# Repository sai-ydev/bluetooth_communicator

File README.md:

# Bluetooth Communicator Badge

This project is my submission for the [Hackaday Sci-Fi Contest](https://hackaday.io/contest/184314-sci-fi-contest). It is a communicator badge from Star Trek. 

It consists of the following components:
1. [BlueNRG-M2SP](https://www.mouser.com/ProductDetail/STMicroelectronics/BLUENRG-M2SP?qs=%252B6g0mu59x7IAMQd6TX9bOA%3D%3D)
2. [BME680](https://www.digikey.com/en/products/detail/bosch-sensortec/BME680/7401317)
3. [LSM6DSO32](https://www.st.com/resource/en/datasheet/lsm6dso32.pdf)

This board can serve two purposes namely: 
1. Pedometer
2. Air Quality Communicator

The first version of the board:

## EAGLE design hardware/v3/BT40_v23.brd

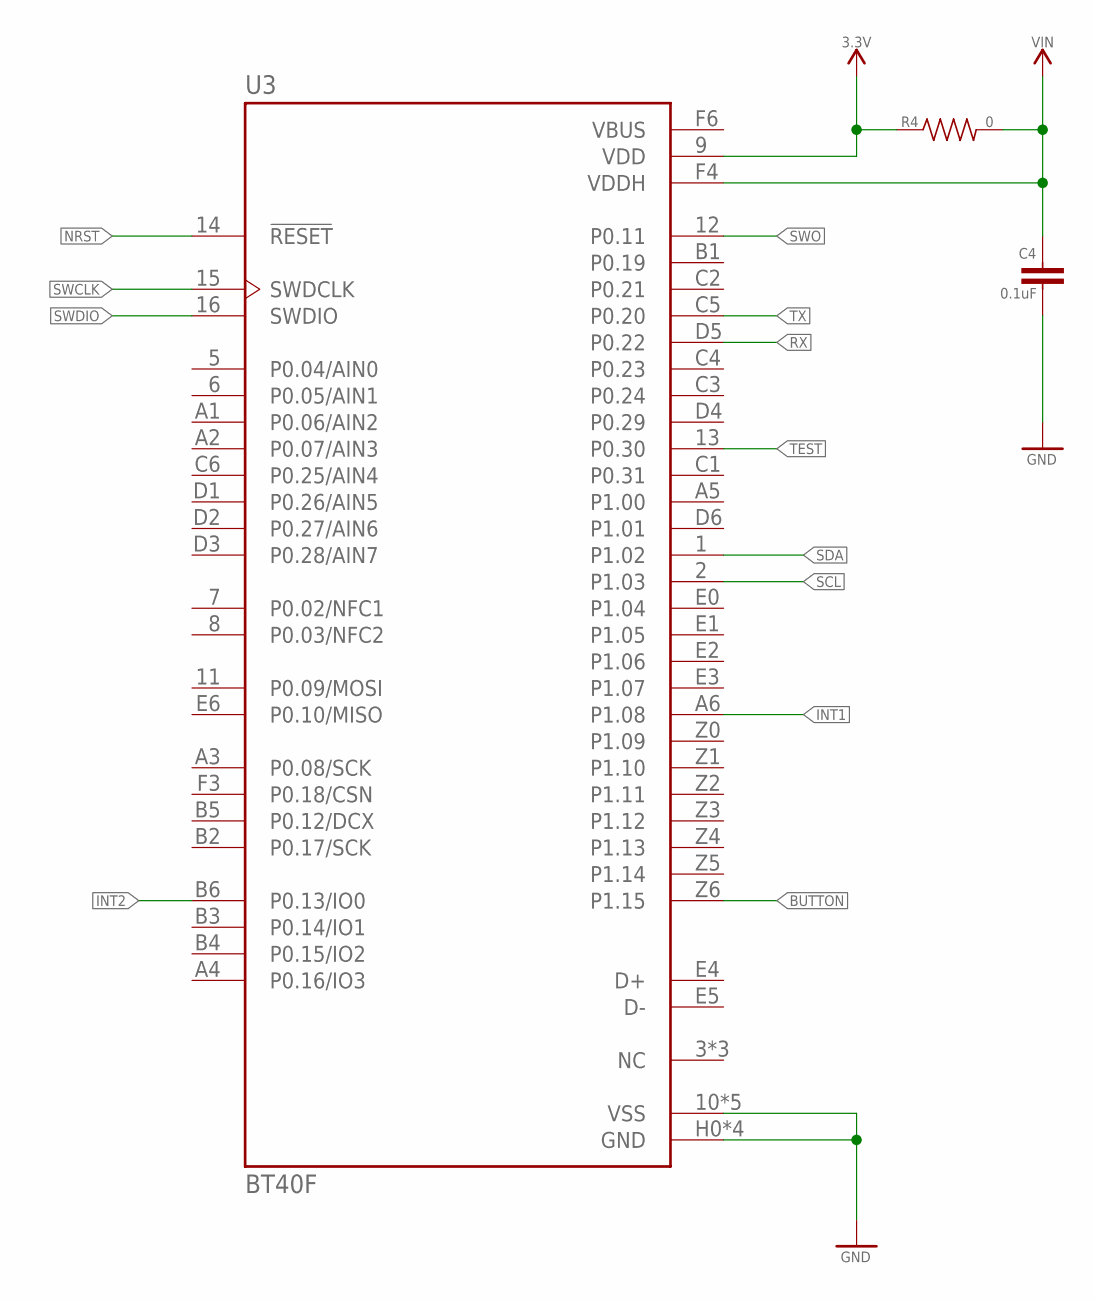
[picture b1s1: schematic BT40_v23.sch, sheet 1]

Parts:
C4: 0.1uF; 0603
R4: 0; 0603
U3: BT40F; XCVR_BT40F

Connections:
3.3V: R4.1, U3.9 (VDD)
BUTTON: U3.Z6 (P1.15); also elsewhere on the board
GND: C4.2, U3.10 (VSS), U3.A0 (VSS), U3.B0 (VSS), U3.C0 (VSS), U3.D0 (VSS), U3.H0 (GND), U3.H1 (GND), U3.H2 (GND), U3.H3 (GND); also elsewhere on the board
INT1: U3.A6 (P1.08); also elsewhere on the board
INT2: U3.B6 (P0.13/IO0); also elsewhere on the board
NRST: U3.14 (!RESET); also elsewhere on the board
RX: U3.D5 (P0.22); also elsewhere on the board
SCL: U3.2 (P1.03); also elsewhere on the board
SDA: U3.1 (P1.02); also elsewhere on the board
SWCLK: U3.15 (SWDCLK); also elsewhere on the board
SWDIO: U3.16 (SWDIO); also elsewhere on the board
SWO: U3.12 (P0.11); also elsewhere on the board
TEST: U3.13 (P0.30); also elsewhere on the board
TX: U3.C5 (P0.20); also elsewhere on the board
VBUS: U3.F6 (VBUS)
VIN: C4.1, R4.2, U3.F4 (VDDH); also elsewhere on the board

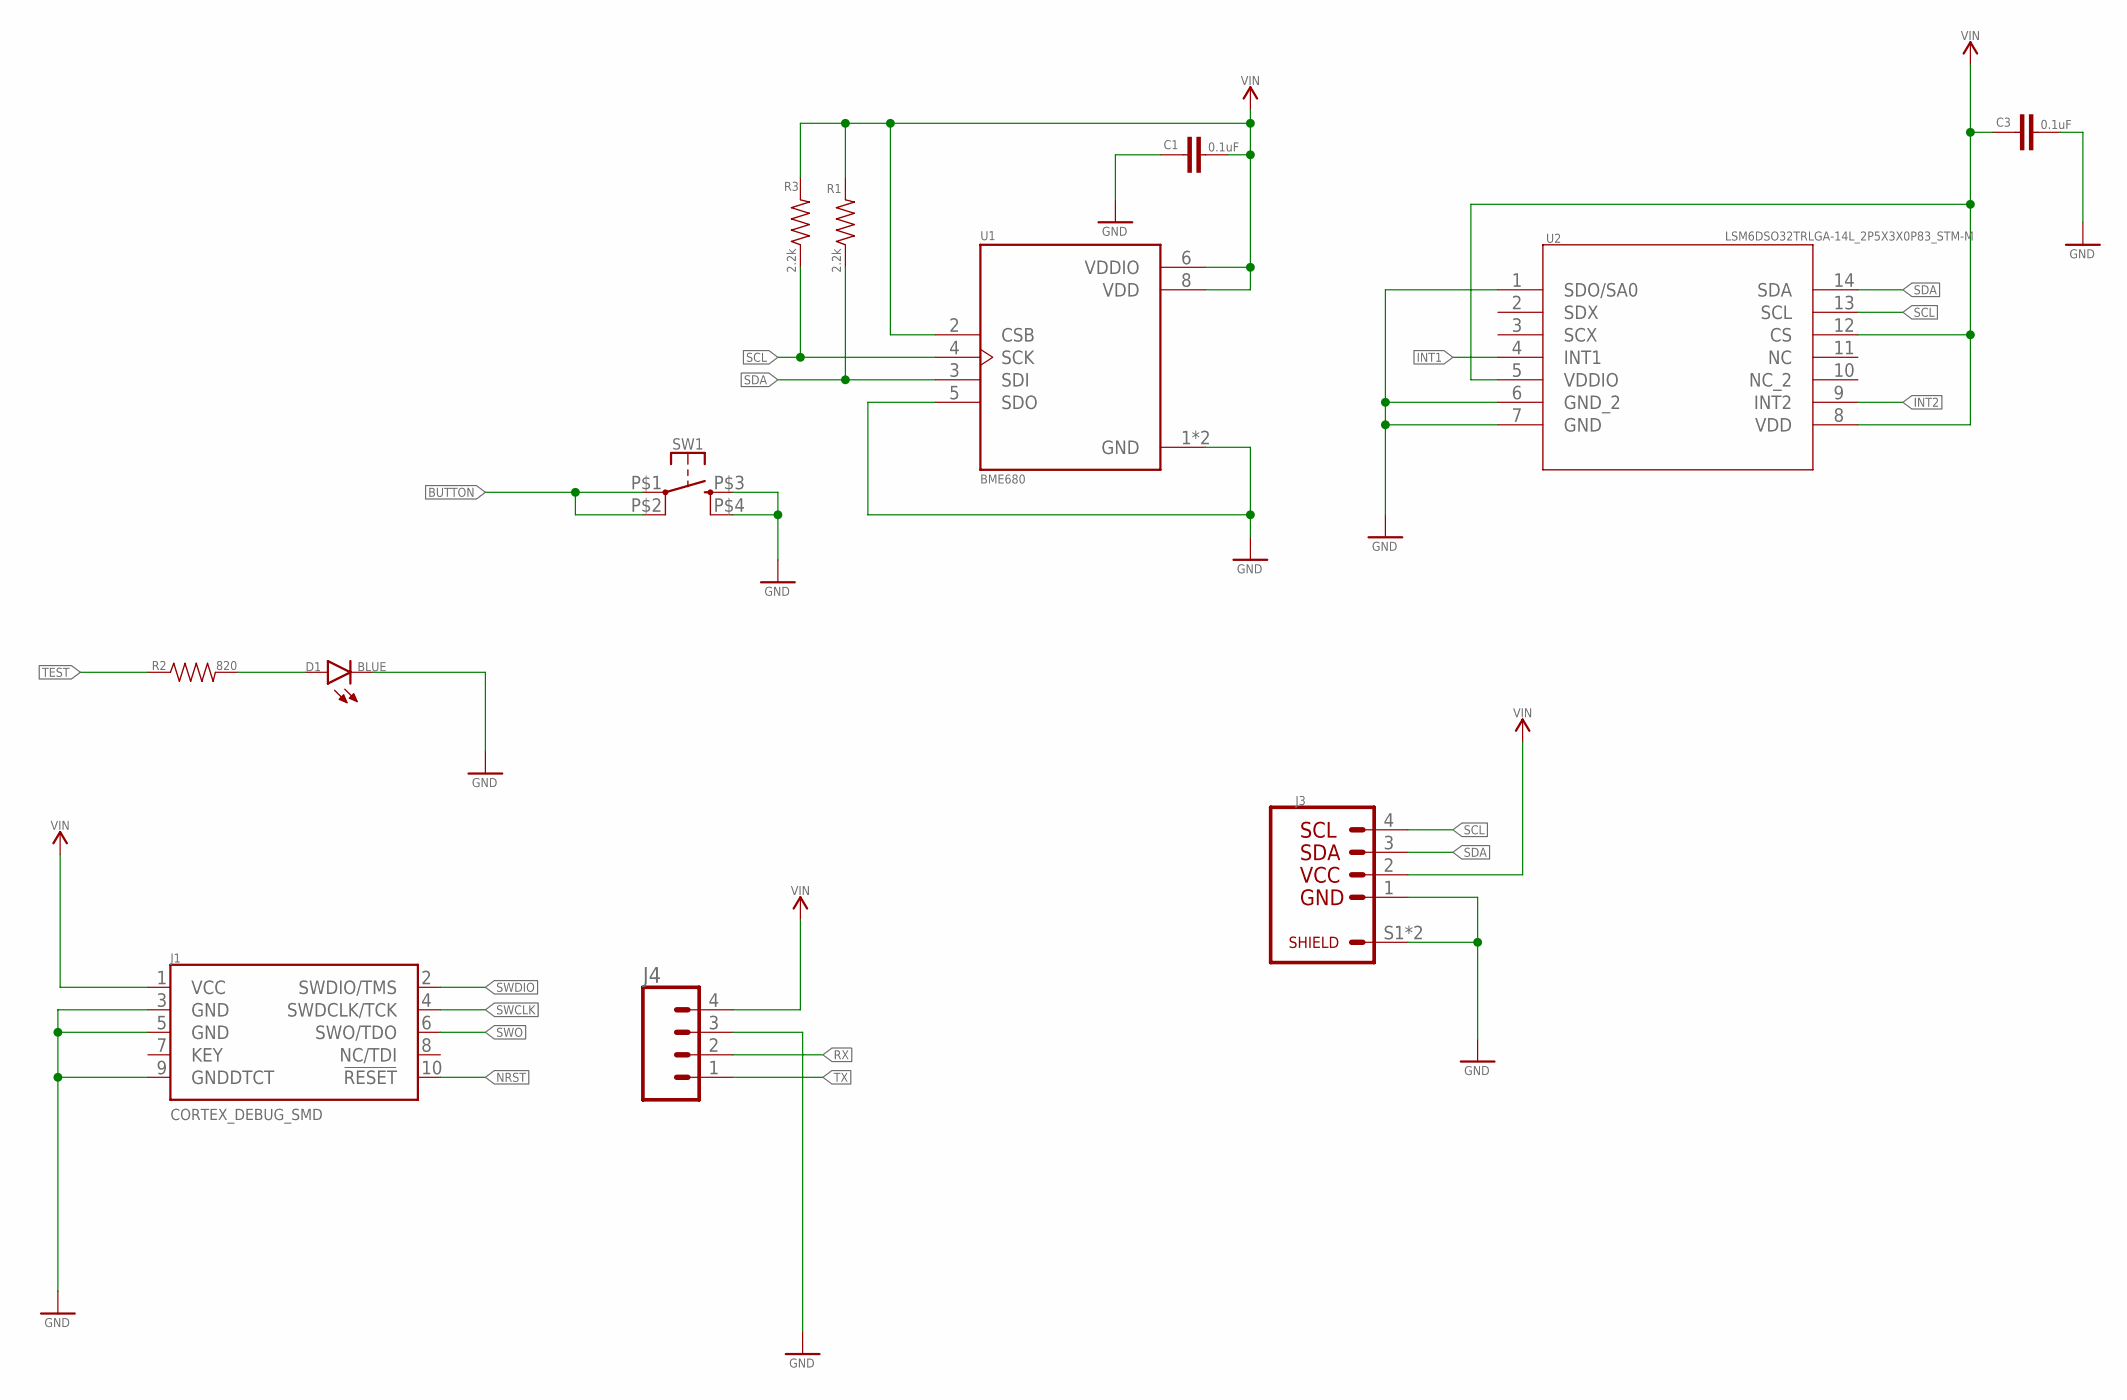
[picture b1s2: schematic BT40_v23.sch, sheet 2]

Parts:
C1, C3: 0.1uF; 0603
D1: BLUE; LED-0603
J1: CORTEX_DEBUG_SMD; SAMTECH_FTSH-105-01
J3: QWIIC; CONN_BM04B-SRSS-TB(LF)(SN)
J4: CONN_04SMD; 1X04_SMD_RA_MALE
R1, R3: 2.2k; 0603
R2: 820; 0603
SW1: REVERSE_SWITCH; REVERSE_TACTILE
U1: BME680; PSON80P300X300X100-8N
U2: LSM6DSO32TRLGA-14L_2P5X3X0P83_STM-M; LGA-14L_2P5X3X0P83_STM-M

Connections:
BUTTON: SW1.P$1 (1), SW1.P$2 (2); also elsewhere on the board
GND: C1.1, C3.2, D1.C, J1.3 (GND), J1.5 (GND), J1.9 (GNDDTCT), J3.1, J3.S1, J3.S2, J4.3 (SDA), SW1.P$3 (3), SW1.P$4 (4), U1.1 (GND), U1.5 (SDO), U1.7 (GND), U2.1 (SDO/SA0), U2.6 (GND_2), U2.7 (GND); also elsewhere on the board
INT1: U2.4 (INT1); also elsewhere on the board
INT2: U2.9 (INT2); also elsewhere on the board
unnamed: D1.A, R2.2
NRST: J1.10 (!RESET); also elsewhere on the board
RX: J4.2 (SCL); also elsewhere on the board
SCL: J3.4, R3.1, U1.4 (SCK), U2.13 (SCL); also elsewhere on the board
SDA: J3.3, R1.1, U1.3 (SDI), U2.14 (SDA); also elsewhere on the board
SWCLK: J1.4 (SWDCLK/TCK); also elsewhere on the board
SWDIO: J1.2 (SWDIO/TMS); also elsewhere on the board
SWO: J1.6 (SWO/TDO); also elsewhere on the board
TEST: R2.1; also elsewhere on the board
TX: J4.1 (VCC); also elsewhere on the board
VIN: C1.2, C3.1, J1.1 (VCC), J3.2, J4.4 (GND), R1.2, R3.2, U1.2 (CSB), U1.6 (VDDIO), U1.8 (VDD), U2.5 (VDDIO), U2.8 (VDD), U2.12 (CS); also elsewhere on the board

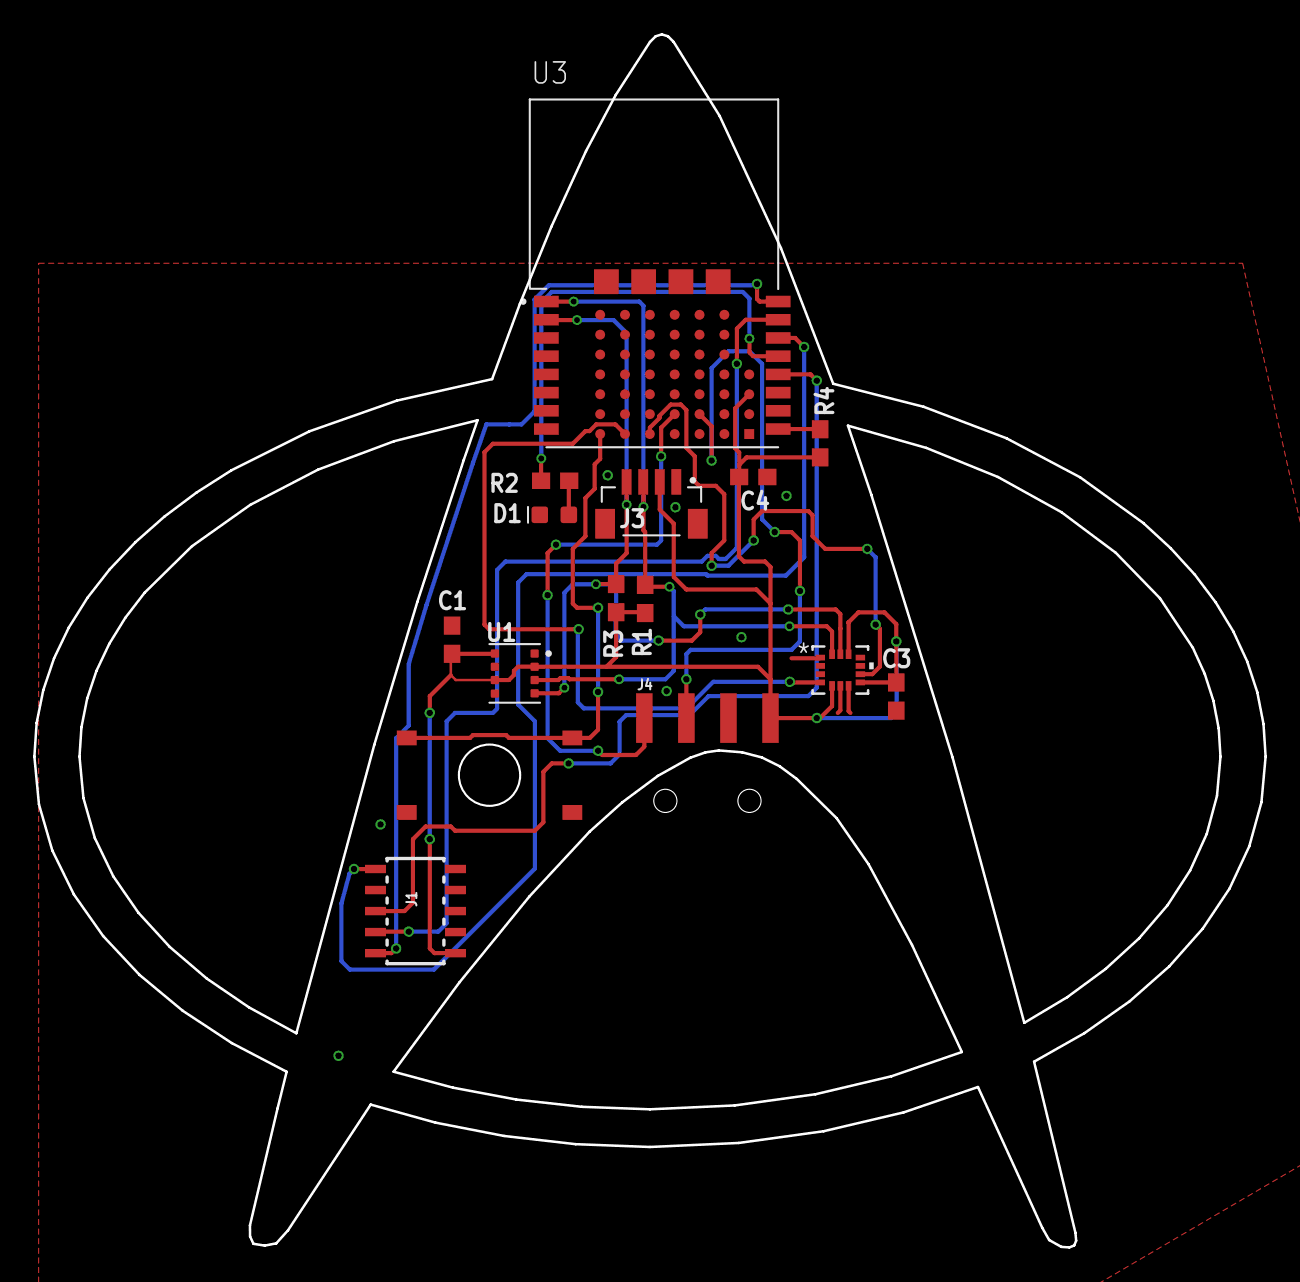
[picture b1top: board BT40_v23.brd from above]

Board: 2 copper layers, 74.3 x 73.2 mm, 15 parts (0 on the bottom side), 16 nets.

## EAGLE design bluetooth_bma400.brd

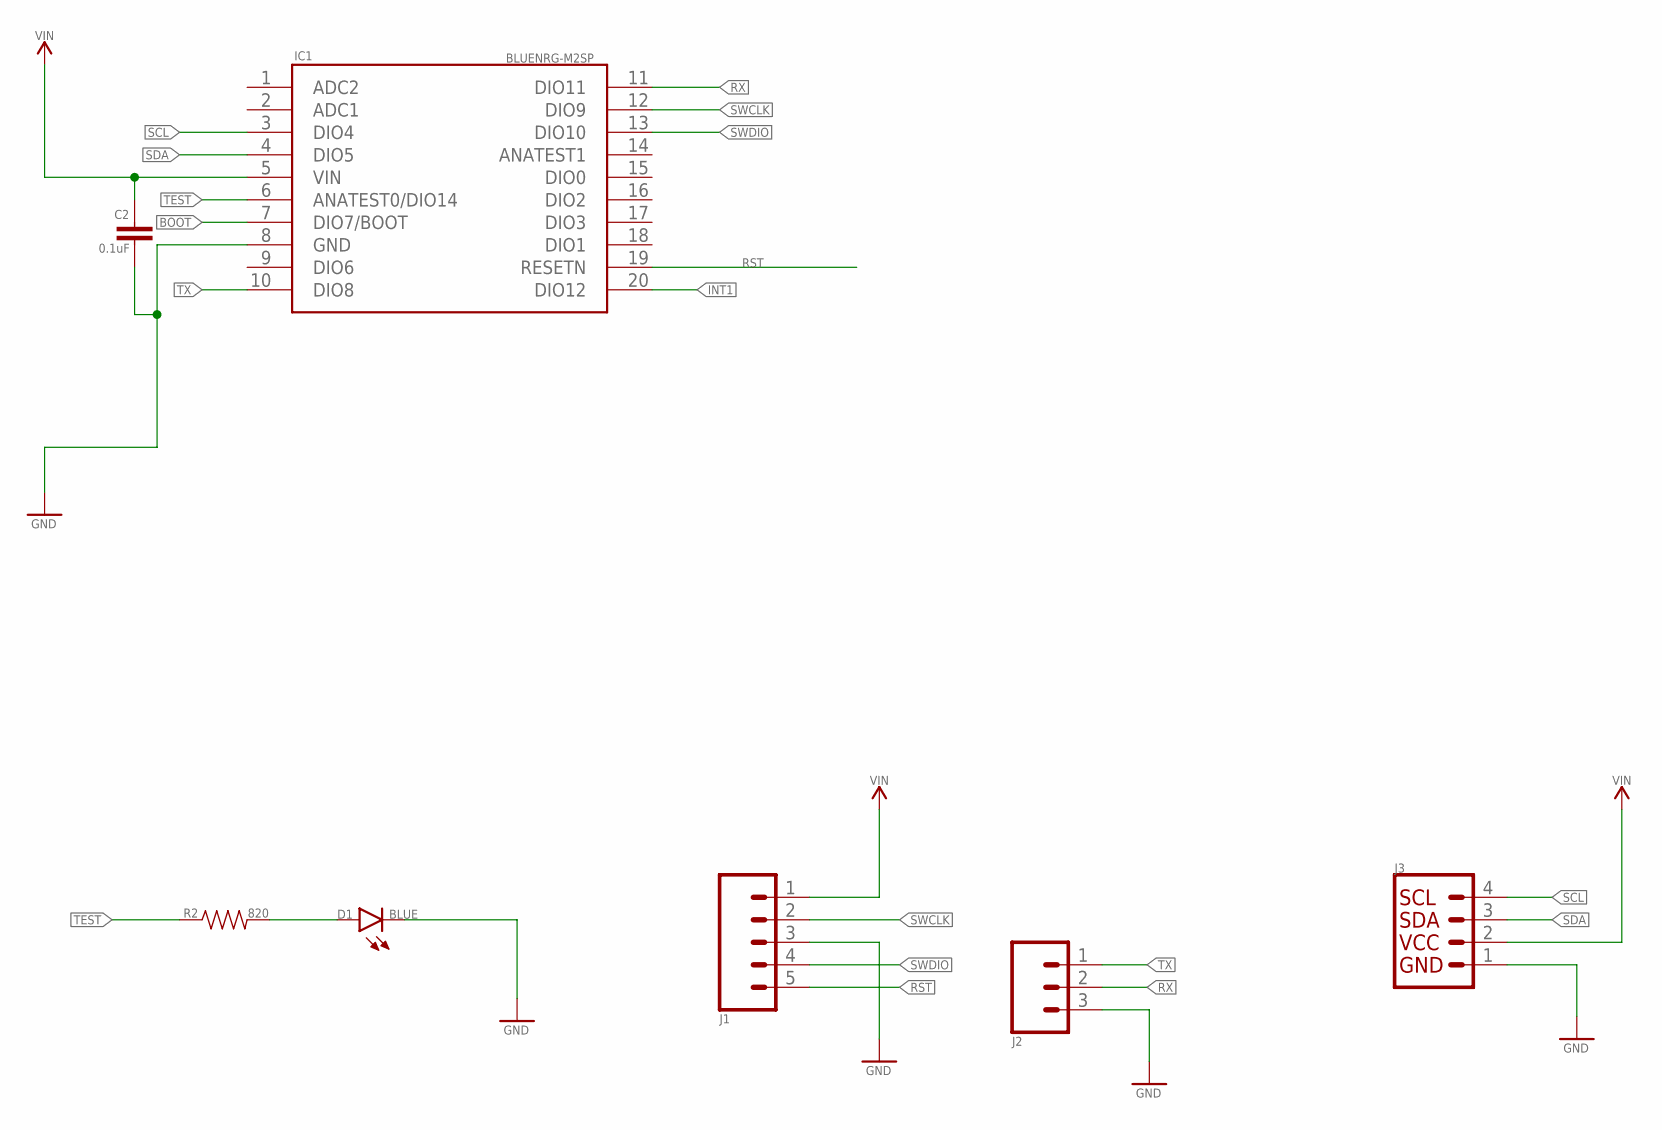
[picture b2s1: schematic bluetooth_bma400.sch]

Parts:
C2: 0.1uF; 0603
D1: BLUE; LED-0603
IC1: BLUENRG-M2SP; BLUENRGM2SP
J1: CONN_05; 1X05
J2: 455-1750-1-ND; 1X03
J3: QWIIC_CONNECTORJS-1MM; 1X04_1MM_RA
R2: 820; 0603

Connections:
BOOT: IC1.7 (DIO7/BOOT)
GND: C2.2, D1.C, IC1.8 (GND), J1.3, J2.3, J3.1
INT1: IC1.20 (DIO12)
unnamed: D1.A, R2.2
RST: IC1.19 (RESETN), J1.5
RX: IC1.11 (DIO11), J2.2
SCL: IC1.3 (DIO4), J3.4
SDA: IC1.4 (DIO5), J3.3
SWCLK: IC1.12 (DIO9), J1.2
SWDIO: IC1.13 (DIO10), J1.4
TEST: IC1.6 (ANATEST0/DIO14), R2.1
TX: IC1.10 (DIO8), J2.1
VIN: C2.1, IC1.5 (VIN), J1.1, J3.2

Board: 2 copper layers, 7 parts (0 on the bottom side), 11 nets, no tracks yet.

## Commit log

2022-04-19 Files
2022-04-19 Updated files
2022-04-20 PCB design + library check-in
2022-04-20 Final version
2022-04-20 Re-org of files.
2022-04-20 v2 gerber file
2022-05-06 v2 design files
2022-09-29 eagle design files
2022-09-29 Changes to design files
2022-09-29 Check-in
2022-09-29 Update to schematic
2022-09-30 Update to design files
2022-09-30 Completed PCB design

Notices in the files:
parts and their libraries:
SparkFun-Capacitors: Licensing: Creative Commons ShareAlike 4.0 International - https://creativecommons.org/licenses/by-sa/4.0
COPYRIGHT: Copyright (C) 2022 Ultra Librarian. All rights reserved.
